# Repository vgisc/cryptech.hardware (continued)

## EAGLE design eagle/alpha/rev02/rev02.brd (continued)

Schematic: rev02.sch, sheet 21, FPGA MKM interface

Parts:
R65: 1.0k; R0402; TOLERANCE 5%
R83, R84, R85: 0; R0603; TOLERANCE 5%
U13: XC7A200TFBG484; FF484; MPN XC7A200T-1FBG484C

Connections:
DIGITIZED_NOISE: U13.W19 (IO_L12P_T1_MRCC_14); also elsewhere on the board
FPGA_CFG_CS_N: R85.1; also elsewhere on the board
FPGA_CFG_CS_N1: R85.2, U13.T19 (IO_L6P_T0_FCS_B_14)
FPGA_CFG_MISO: R84.1; also elsewhere on the board
FPGA_CFG_MISO1: R84.2, U13.R22 (IO_L1N_T0_D01_DIN_14)
FPGA_CFG_MOSI: R83.1; also elsewhere on the board
FPGA_CFG_MOSI1: R83.2, U13.P22 (IO_L1P_T0_D00_MOSI_14)
FPGA_GPIO_LED_0: U13.T20 (IO_L6N_T0_D08_VREF_14); also elsewhere on the board
FPGA_GPIO_LED_1: U13.W21 (IO_L7P_T1_D09_14); also elsewhere on the board
FPGA_GPIO_LED_2: U13.W22 (IO_L7N_T1_D10_14); also elsewhere on the board
FPGA_GPIO_LED_3: U13.AA20 (IO_L8P_T1_D11_14); also elsewhere on the board
MKM_FPGA_CS_N: U13.T21 (IO_L4P_T0_D04_14); also elsewhere on the board
MKM_FPGA_MISO: U13.R19 (IO_L5N_T0_D07_14); also elsewhere on the board
MKM_FPGA_MOSI: U13.P19 (IO_L5P_T0_D06_14); also elsewhere on the board
MKM_FPGA_SCK: U13.U21 (IO_L4N_T0_D05_14); also elsewhere on the board
unnamed: R65.1, U13.U22 (IO_L3P_T0_DQS_PUDC_B_14)
VCCO_3V3: R65.2, U13.M14 (VCCO_14), U13.P18 (VCCO_14), U13.R15 (VCCO_14), U13.T22 (VCCO_14), U13.U19 (VCCO_14), U13.Y20 (VCCO_14); also elsewhere on the board

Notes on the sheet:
*) Lower Right Bank
DIGITIZED_NOISE signal should go into either W19 or Y18 (i.e. into one of the two positive (master) sides of the two available MRCC differential pairs)
*) Signals, that are allowed to be swapped, can be be swapped with each other and/or moved to different pins within their bank.
<-- FPGA_GPIO_* and FPGA_IRQ_N_* signals can be swapped
<-- Disable pull-ups on all pins during configuration
FPGA MKM interface

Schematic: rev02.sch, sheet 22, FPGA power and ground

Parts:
U13: XC7A200TFBG484; FF484; MPN XC7A200T-1FBG484C

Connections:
FPGA_VCCAUX_1V8: U13.H12 (VCCAUX), U13.K12 (VCCAUX), U13.M12 (VCCAUX), U13.P12 (VCCAUX), U13.R11 (VCCAUX); also elsewhere on the board
FPGA_VCCINT_1V0: U13.H8 (VCCINT), U13.H10 (VCCINT), U13.J7 (VCCINT), U13.J9 (VCCINT), U13.J11 (VCCBRAM), U13.K8 (VCCINT), U13.L7 (VCCINT), U13.L11 (VCCBRAM), U13.M8 (VCCINT), U13.N7 (VCCINT), U13.N11 (VCCBRAM), U13.P8 (VCCINT), U13.P10 (VCCINT), U13.R7 (VCCINT), U13.R9 (VCCINT), U13.T8 (VCCINT), U13.T10 (VCCINT); also elsewhere on the board
GND: U13.A2 (GND), U13.A3 (GND), U13.A5 (GND), U13.A7 (GND), U13.A9 (GND), U13.A11 (GND), U13.A12 (GND), U13.A22 (GND), U13.AA2 (GND), U13.AA12 (GND), U13.AA22 (GND), U13.AB9 (GND), U13.AB19 (GND), U13.B3 (GND), U13.B12 (GND), U13.B19 (GND), U13.C3 (GND), U13.C6 (GND), U13.C10 (GND), U13.C12 (GND), U13.C16 (GND), U13.D3 (GND), U13.D4 (GND), U13.D8 (GND), U13.D12 (GND), U13.D13 (GND), U13.E4 (GND), U13.E5 (GND), U13.E7 (GND), U13.E9 (GND), U13.E11 (GND), U13.E20 (GND), U13.F5 (GND), U13.F11 (GND), U13.F17 (GND), U13.G5 (GND), U13.G6 (GND), U13.G7 (GND), U13.G8 (GND), U13.G9 (GND), U13.G10 (GND), U13.G12 (GND), U13.G14 (GND), U13.H1 (GND), U13.H7 (GND), U13.H9 (GND), U13.H11 (GND), U13.H21 (GND), U13.J8 (GND), U13.J10 (GND), U13.J12 (GND), U13.J18 (GND), U13.K5 (GND), U13.K7 (GND), U13.K11 (GND), U13.K15 (GND), U13.L2 (GND), U13.L8 (GND), U13.L22 (GND), U13.M7 (GND), U13.M11 (GND), U13.M19 (GND), U13.N6 (GND), U13.N8 (GND), U13.N16 (GND), U13.P3 (GND), U13.P7 (GND), U13.P9 (GND), U13.P11 (GND), U13.P13 (GND), U13.R8 (GND), U13.R10 (GND), U13.R12 (GND), U13.R20 (GND), U13.T7 (GND), U13.T9 (GND), U13.T11 (GND), U13.T17 (GND), U13.U4 (GND), U13.U14 (GND), U13.V1 (GND), U13.V11 (GND), U13.V21 (GND), U13.W8 (GND), U13.W18 (GND), U13.Y5 (GND), U13.Y15 (GND); also elsewhere on the board

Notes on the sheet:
*) Power - AUX
*) Power - CORE & BRAM
*) Ground Pins
FPGA power and ground

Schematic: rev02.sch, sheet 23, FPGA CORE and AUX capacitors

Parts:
C123, C127: 330 uF; SMC_D; TOLERANCE 10%
C124, C125, C128, C129, C130, C131, C134, C135, C138, C142, C143, C146, C147, C150, C151, C154, C155, C158, C159, C162, C163, C164: 0.47 uF; C0402; TOLERANCE 10%
C126, C133, C137: 47 uF; C1210; TOLERANCE 20%
C132, C136, C139, C140, C141, C144, C145, C148, C149, C152, C153, C156, C157, C160, C161: 4.7 uF; C0603; TOLERANCE 10%

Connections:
FPGA_VCCAUX_1V8: C126.1, C132.1, C136.1, C139.1, C143.1, C147.1, C151.1, C155.1, C159.1; also elsewhere on the board
FPGA_VCCINT_1V0: C123.+, C124.1, C125.1, C127.+, C128.1, C129.1, C130.1, C131.1, C133.1, C134.1, C135.1, C137.1, C138.1, C140.1, C141.1, C142.1, C144.1, C145.1, C146.1, C148.1, C149.1, C150.1, C152.1, C153.1, C154.1, C156.1, C157.1, C158.1, C160.1, C161.1, C162.1, C163.1, C164.1; also elsewhere on the board
GND: C123.-, C124.2, C125.2, C126.2, C127.-, C128.2, C129.2, C130.2, C131.2, C132.2, C133.2, C134.2, C135.2, C136.2, C137.2, C138.2, C139.2, C140.2, C141.2, C142.2, C143.2, C144.2, C145.2, C146.2, C147.2, C148.2, C149.2, C150.2, C151.2, C152.2, C153.2, C154.2, C155.2, C156.2, C157.2, C158.2, C159.2, C160.2, C161.2, C162.2, C163.2, C164.2; also elsewhere on the board

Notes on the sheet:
<-- Place small 0.47 uF caps right under the BGA package <-- Place medium 4.7 uF caps very close to the BGA package <-- Place large 47 uF and 330 uF caps not far from the BGA package <-- Distribute smaller caps evenly under the BGA package <-- Distribute larger caps evenly around the BGA package
*) Decoupling capacitors for VCCINT and VCCBRAM
<-- Place small 0.47 uF caps right under the BGA package <-- Place medium 4.7 uF caps very close to the BGA package <-- Place large 47 uF caps not far from the BGA package <-- Try to place smaller caps next to FPGA balls
*) Decoupling capacitors for VCCAUX
FPGA CORE and AUX capacitors

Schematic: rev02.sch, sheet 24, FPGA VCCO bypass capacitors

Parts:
C165, C166, C167, C168: 47 uF; C1210; TOLERANCE 20%
C169, C170, C171, C172, C173, C174, C175, C176, C177, C178, C179, C180: 4.7 uF; C0603; TOLERANCE 10%
C181, C182, C183, C184, C185, C186, C187, C188, C189, C190, C191, C192, C193, C194, C195, C196, C197, C198, C199, C200, C201, C202, C203, C204: 0.47 uF; C0402; TOLERANCE 10%

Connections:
GND: C165.2, C166.2, C167.2, C168.2, C169.2, C170.2, C171.2, C172.2, C173.2, C174.2, C175.2, C176.2, C177.2, C178.2, C179.2, C180.2, C181.2, C182.2, C183.2, C184.2, C185.2, C186.2, C187.2, C188.2, C189.2, C190.2, C191.2, C192.2, C193.2, C194.2, C195.2, C196.2, C197.2, C198.2, C199.2, C200.2, C201.2, C202.2, C203.2, C204.2; also elsewhere on the board
VCCO_3V3: C165.1, C166.1, C167.1, C168.1, C169.1, C170.1, C171.1, C172.1, C173.1, C174.1, C175.1, C176.1, C177.1, C178.1, C179.1, C180.1, C181.1, C182.1, C183.1, C184.1, C185.1, C186.1, C187.1, C188.1, C189.1, C190.1, C191.1, C192.1, C193.1, C194.1, C195.1, C196.1, C197.1, C198.1, C199.1, C200.1, C201.1, C202.1, C203.1, C204.1; also elsewhere on the board

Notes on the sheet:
<-- Place small 0.47 uF caps right under the BGA package <-- Place medium 4.7 uF caps very close to the BGA package <-- Place large 47 uF caps not far from the BGA package <-- Place one of four 47 uF caps on every side of the BGA p. <-- Distribute six sets of caps among six FPGA I/O banks
*) Decoupling capacitors for VCCO
FPGA VCCO bypass capacitors

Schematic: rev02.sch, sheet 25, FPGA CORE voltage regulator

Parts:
C205, C206: 22 uF; C1210; TOLERANCE 20%
C207: 0.047 uF; C0402; TOLERANCE 10%
C208: 27pF; C0402; TOLERANCE 5%
C209, C210: 47 uF; C1210; TOLERANCE 20%
FB7: 0; 1206
R66: 4.7k; R0402; TOLERANCE 5%
R67: 0; R0402
R68: 150k; R0402; TOLERANCE 1%
R69: 226k; R0402; TOLERANCE 1%
R70: 100; R0402; TOLERANCE 5%
U16: EN5364QI; QFN68_8X11X1.85

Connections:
FPGA_VCCINT_1V0: FB7.2; also elsewhere on the board
GND: C205.2, C206.2, C207.2, C209.2, C210.2, R69.1, R70.1, U16.1 (PGND), U16.2 (PGND), U16.3 (PGND), U16.4 (PGND), U16.27 (PGND), U16.28 (PGND), U16.29 (PGND), U16.30 (PGND), U16.31 (PGND), U16.32 (PGND), U16.33 (PGND), U16.55 (AGND), U16.64 (PGND), U16.65 (PGND), U16.66 (PGND), U16.67 (PGND), U16.68 (PGND), U16.P$69 (PGND), U16.P$70 (PGND), U16.P$71 (PGND); also elsewhere on the board
unnamed: C207.1, U16.59 (SS)
unnamed: R66.1, U16.51 (EN_PB)
unnamed: R67.1, U16.63 (VSENSE)
unnamed: C208.1, C209.1, C210.1, FB7.1, R67.2, R68.2, R70.2, U16.5 (VOUT), U16.6 (VOUT), U16.7 (VOUT), U16.8 (VOUT), U16.9 (VOUT), U16.10 (VOUT), U16.11 (VOUT), U16.12 (VOUT), U16.13 (VOUT)
unnamed: C208.2, R68.1, R69.2, U16.56 (VFB)
POK_VCCINT: U16.54 (POK); also elsewhere on the board
PWR_ENA_VCCINT: U16.52 (ENABLE); also elsewhere on the board
VCC_5V0: C205.1, C206.1, R66.2, U16.34 (PVIN), U16.35 (PVIN), U16.36 (PVIN), U16.37 (PVIN), U16.38 (PVIN), U16.39 (PVIN), U16.40 (PVIN), U16.41 (PVIN), U16.42 (PVIN), U16.43 (PVIN), U16.53 (AVIN); also elsewhere on the board

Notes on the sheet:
*) FPGA Power Subsystem -- CORE
*) VCCINT = 0.6V x (1 + 150 / 226) = 0.998V *) OCP_ADJ is not used (default over-current threshold) *) MARx are not used (output at nominal 100%) *) S_IN/S_OUT are not used (single regulator mode) *) S_DELAY is not used (single regulator mode) *) M/S is not used (parallel operation not needed) *) E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
FPGA CORE voltage regulators

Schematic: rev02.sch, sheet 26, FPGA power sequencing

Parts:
C211, C212, C213: 0.1 uF; C0402; TOLERANCE 10%
D2, D3, D4: BAT54; SOT23
LED18: GREEN; CHIP-LED0603
Q6: 2N7002; SOT23
R72, R74, R76: 100k; R0402; TOLERANCE 1%
R73, R75, R77: 4.7k; R0402; TOLERANCE 5%
R78: 330; R0402; TOLERANCE 5%

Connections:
GND: C211.2, C212.2, C213.2, Q6.2 (S); also elsewhere on the board
unnamed: LED18.C, Q6.3 (D)
unnamed: LED18.A, R78.1
POK_VCCAUX: D3.3 (C), R73.1, R74.1; also elsewhere on the board
POK_VCCINT: D4.3 (C), R75.1, R76.1; also elsewhere on the board
POK_VCCO: Q6.1 (G), R77.1; also elsewhere on the board
PWR_ENA_VCCAUX: C213.1, D4.1 (A), R76.2; also elsewhere on the board
PWR_ENA_VCCINT: C211.1, D2.1 (A), R72.2; also elsewhere on the board
PWR_ENA_VCCO: C212.1, D3.1 (A), R74.2; also elsewhere on the board
VCC_5V0: D2.3 (C), R72.1, R73.2, R75.2, R77.2, R78.2; also elsewhere on the board

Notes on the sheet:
*) Recommended power-up sequence: 1) VCCINT 2) VCCAUX 3) VCCO RC network values are preliminary, should be tweaked after experiments
--->
*) "Power OK" LED, should be of green color
FPGA power sequencing

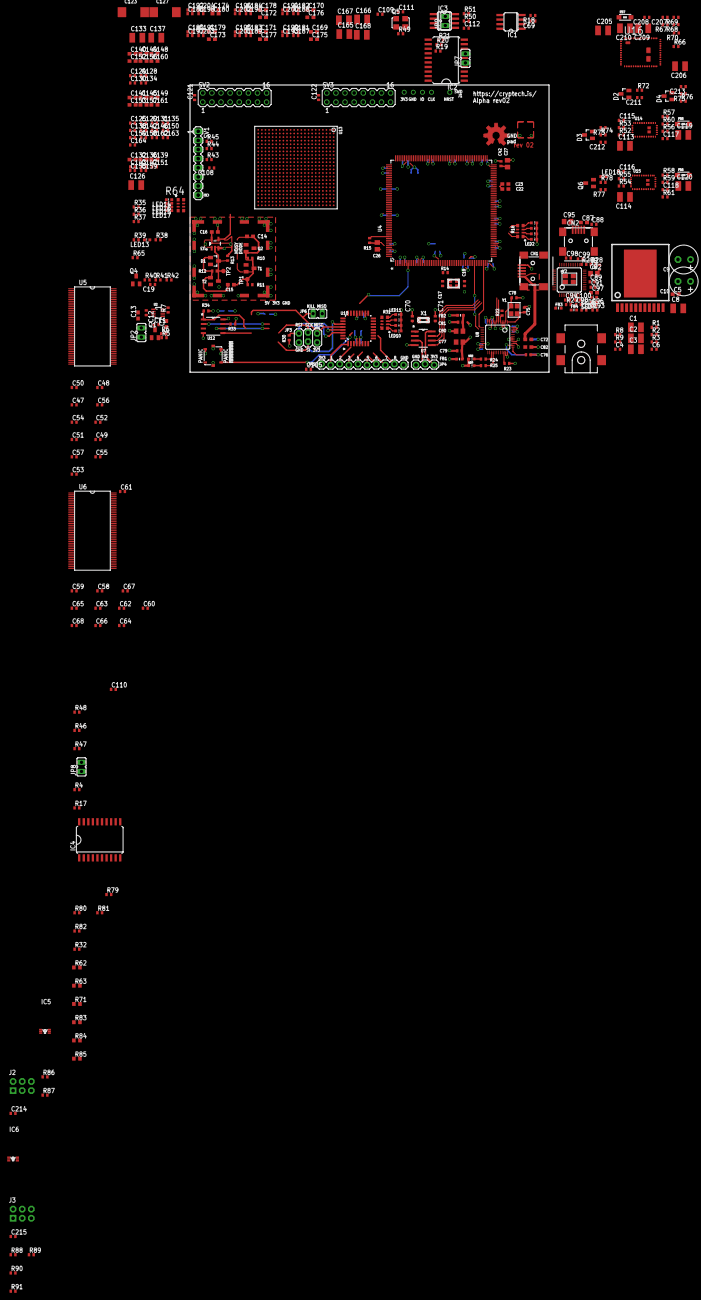
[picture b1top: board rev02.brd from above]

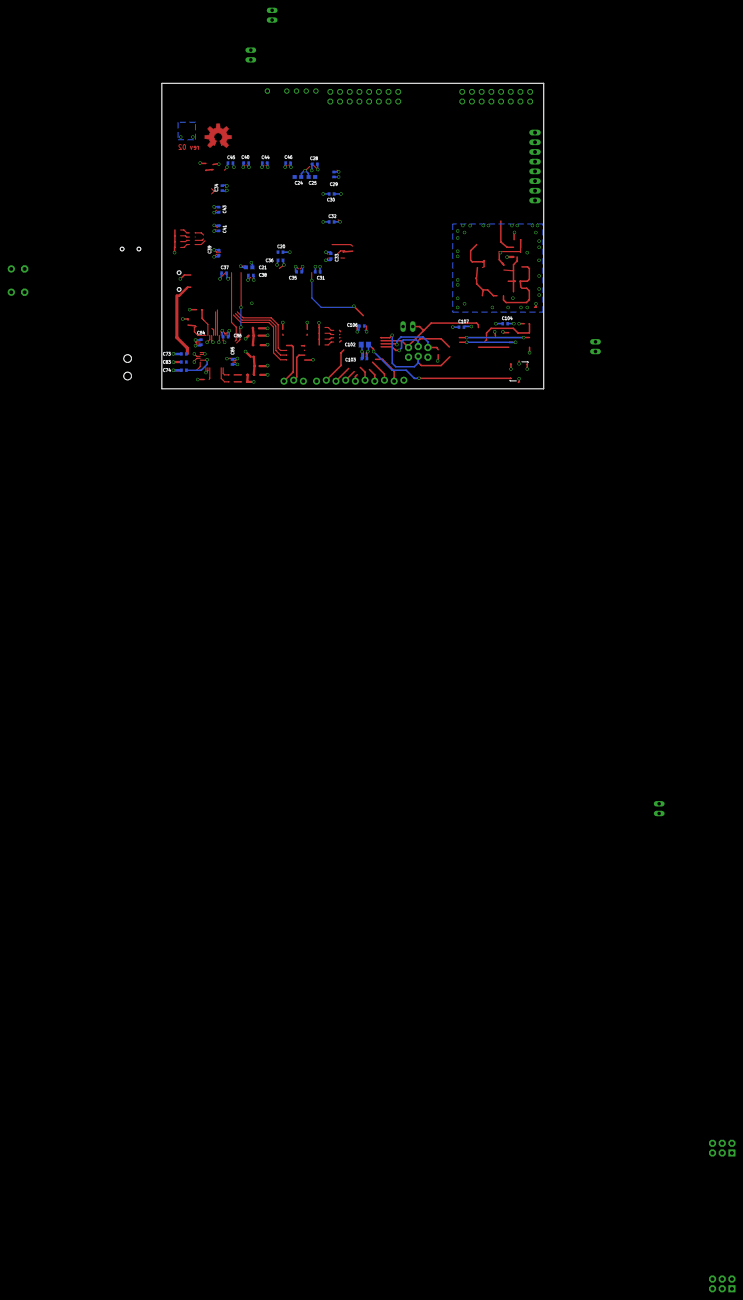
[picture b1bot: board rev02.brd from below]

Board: 4 copper layers, 100.0 x 80.0 mm, 389 parts (33 on the bottom side), 304 nets.

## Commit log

2015-12-01 init, import dev-bridge board
2015-12-01 init, copy of dev-bridge rev01
2015-12-01 rename to match revision
2015-12-01 copied in 15 sheets of FPGA design from pavel
2015-12-01 remove components that will not be on the Alpha board
2015-12-01 fixed most of the FMC bus, grouped components.
2015-12-01 more changes, end of today
2015-12-03 fix some errata
2015-12-04 finished merging Pavel's FPGA schematics into the dev-bridge schematics.
2015-12-10 lots of updates after call with Pavel
2015-12-14 add more parts of the schematic (SRAM, analog switch for config mem)
2015-12-14 init
2015-12-16 connect first SDRAM, add USB MGMT UART.
2015-12-19 updates after todays call with Pavel
2015-12-23 connect ARM side of SD/MMC, MGMT USB
2015-12-27 rearrange STM32F429 symbol after functionality instead of hardware
    Now that it is more known what functionality we want to use in the STM32,
    it makes much more sense (and will help reviewers a great deal) to have
    the symbol in the schematics arranged after used functionality rather than
    after how the hardware pinout is.
2015-12-28 add SPI mux for FPGA cfg memory, and some other minor things.
2015-12-28 import FT232H from separate library
2015-12-28 add device prefixes and renumber all components
2015-12-28 optimize BOM a bit, change more 0603s to 0402s
2015-12-28 update PDF
2016-01-30 First set of updates based on review feedback.
2016-02-04 More schematic updates after review with Pavel.
2016-02-09 Maybe final set of review feedback updates.
2016-02-14 Add FPGA part number and pull-ups to ARM UART RXs
2016-02-15 Bugfix copy-paste mistake in USB MGMT UART header.
    Also change pinout of header after input from Peter.
2016-02-15 Update text on first page (from Joachim).
2016-04-01 Gerber and drill files for Alpha rev02, as received from Pavel/Infotecs.
    Source is cryptech_gerbers_31032016.zip with SHA256
    15b68554ebb61d82527329f32a8ab48c396cace66ac29ff35f47bd8c977b0689
2016-07-21 move to subdirectory
2016-07-21 Manufacturing files for rev03, as received from Pavel.
    Source is CrypTech_Mfg_30052016.rar with SHA256
    c2206f43d93162d65830f74b7dc228d99ac1ef10c5c52b2644cd3b81dfc76def
2016-07-21 reorganize
2016-07-21 Altium Designer source files for rev03, as received from Pavel.
    Source is CrypTech_Project_30052016.rar with SHA256
    9d4c4401a560a3dfd69e37b5a76283ca573f91c96ae82eb587724bb610d091a7
